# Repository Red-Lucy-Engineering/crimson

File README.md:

# "crimson" OSHW compact foldable mechanical keyboard

## Roadmap
- [x] Schematics mk1 finished
- [x] PCB design mk1 finished
- [ ] 3D printable Chassis designed in CAD
- [ ] Keycaps 3D printable in ABS
- [ ] firmware finished
- [ ] first version assembled irl
- [ ] first version thoroughly tested
- [ ] first version on sale

## Specs
- TKL -> 87 ULP Cherry Tactile Switches
- Foldable -> preferrably in thirds
- 3D printable chassis and caps
- ZMK firmware based on nice!nano V2 Microcontroller

## BOM

| Amount | Part                         |
|--------|------------------------------|
| 1      | crimson PCB                  |
| 86     | 1N4148W Diode                |
| 86     | Cherry ULP tactile switch    |
| 1      | 6mm tactile switch           |
| 1      | PCM12 SPDT switch            |
| 1      | nice!nano V2 microcontroller |
| 1      | 74HC595 TSSOP-16             |
| 1      | 0805 0,1uF capacitor         |
| 43     | Wires                        |

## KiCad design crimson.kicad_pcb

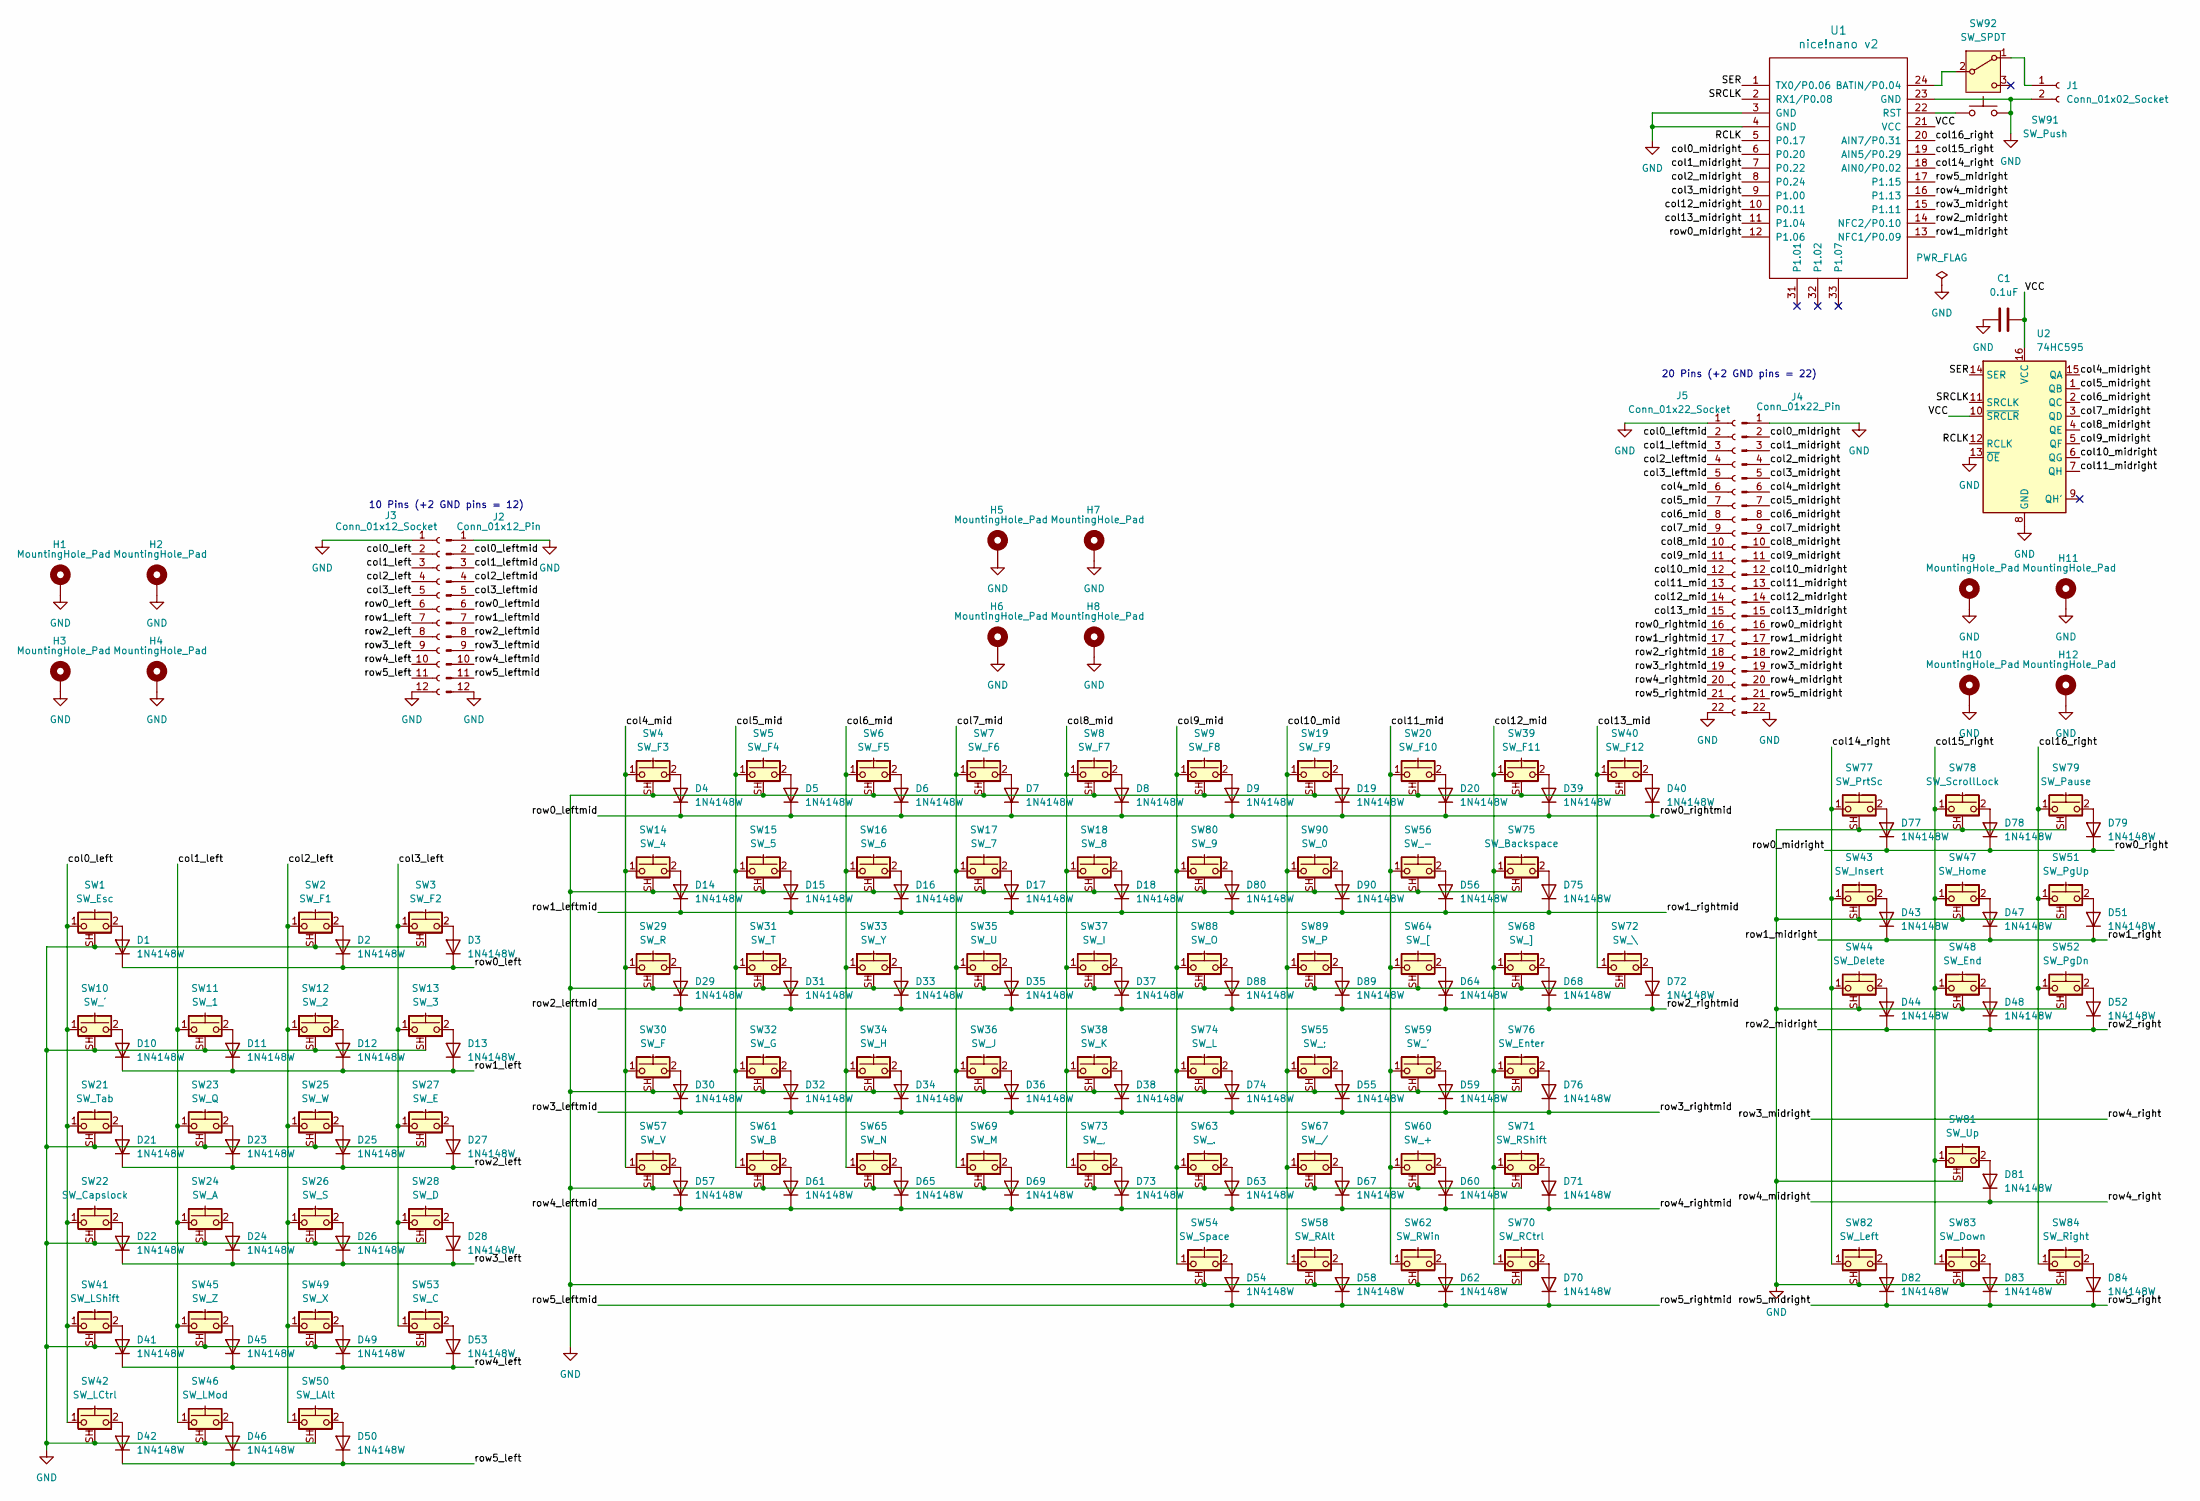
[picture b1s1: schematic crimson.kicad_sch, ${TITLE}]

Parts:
C1: 0.1uF; C_0805_2012Metric_Pad1.18x1.45mm_HandSolder
D1, D2, D3, D4, D5, D6, D7, D8, D9, D10, D11, D12, D13, D14, D15, D16, D17, D18, D19, D20, D21, D22, D23, D24, D25, D26, D27, D28, D29, D30, D31, D32, D33, D34, D35, D36, D37, D38, D39, D40, D41, D42, D43, D44, D45, D46, D47, D48, D49, D50, D51, D52, D53, D54, D55, D56, D57, D58, D59, D60, D61, D62, D63, D64, D65, D67, D68, D69, D70, D71, D72, D73, D74, D75, D76, D77, D78, D79, D80, D81, D82, D83, D84, D88, D89, D90: 1N4148W; D_SOD-123
H1, H2, H3, H4, H5, H6, H7, H8, H9, H10, H11, H12: MountingHole_Pad; MountingHole_2.2mm_M2_DIN965_Pad
J1: Conn_01x02_Socket; JST_PH_S2B-PH-K_1x02_P2.00mm_Horizontal
J2: Conn_01x12_Pin; PinHeader_1x12_P2.00mm_Vertical
J3: Conn_01x12_Socket; PinSocket_1x12_P2.00mm_Vertical
J4: Conn_01x22_Pin; PinSocket_1x22_P2.00mm_Vertical
J5: Conn_01x22_Socket; PinSocket_1x22_P2.00mm_Vertical
SW1: SW_Esc; Cherry_ULP_TH
SW2: SW_F1; Cherry_ULP_TH
SW3: SW_F2; Cherry_ULP_TH
SW4: SW_F3; Cherry_ULP_TH
SW5: SW_F4; Cherry_ULP_TH
SW6: SW_F5; Cherry_ULP_TH
SW7: SW_F6; Cherry_ULP_TH
SW8: SW_F7; Cherry_ULP_TH
SW9: SW_F8; Cherry_ULP_TH
SW10: SW_´; Cherry_ULP_TH
SW11: SW_1; Cherry_ULP_TH
SW12: SW_2; Cherry_ULP_TH
SW13: SW_3; Cherry_ULP_TH
SW14: SW_4; Cherry_ULP_TH
SW15: SW_5; Cherry_ULP_TH
SW16: SW_6; Cherry_ULP_TH
SW17: SW_7; Cherry_ULP_TH
SW18: SW_8; Cherry_ULP_TH
SW19: SW_F9; Cherry_ULP_TH
SW20: SW_F10; Cherry_ULP_TH
SW21: SW_Tab; Cherry_ULP_TH
SW22: SW_Capslock; Cherry_ULP_TH
SW23: SW_Q; Cherry_ULP_TH
SW24: SW_A; Cherry_ULP_TH
SW25: SW_W; Cherry_ULP_TH
SW26: SW_S; Cherry_ULP_TH
SW27: SW_E; Cherry_ULP_TH
SW28: SW_D; Cherry_ULP_TH
SW29: SW_R; Cherry_ULP_TH
SW30: SW_F; Cherry_ULP_TH
SW31: SW_T; Cherry_ULP_TH
SW32: SW_G; Cherry_ULP_TH
SW33: SW_Y; Cherry_ULP_TH
SW34: SW_H; Cherry_ULP_TH
SW35: SW_U; Cherry_ULP_TH
SW36: SW_J; Cherry_ULP_TH
SW37: SW_I; Cherry_ULP_TH
SW38: SW_K; Cherry_ULP_TH
SW39: SW_F11; Cherry_ULP_TH
SW40: SW_F12; Cherry_ULP_TH
SW41: SW_LShift; Cherry_ULP_TH
SW42: SW_LCtrl; Cherry_ULP_TH
SW43: SW_Insert; Cherry_ULP_TH
SW44: SW_Delete; Cherry_ULP_TH
SW45: SW_Z; Cherry_ULP_TH
SW46: SW_LMod; Cherry_ULP_TH
SW47: SW_Home; Cherry_ULP_TH
SW48: SW_End; Cherry_ULP_TH
SW49: SW_X; Cherry_ULP_TH
SW50: SW_LAlt; Cherry_ULP_TH
SW51: SW_PgUp; Cherry_ULP_TH
SW52: SW_PgDn; Cherry_ULP_TH
SW53: SW_C; Cherry_ULP_TH
SW54: SW_Space; Cherry_ULP_TH
SW55: SW_;; Cherry_ULP_TH
SW56: SW_-; Cherry_ULP_TH
SW57: SW_V; Cherry_ULP_TH
SW58: SW_RAlt; Cherry_ULP_TH
SW59: SW_'; Cherry_ULP_TH
SW60: SW_+; Cherry_ULP_TH
SW61: SW_B; Cherry_ULP_TH
SW62: SW_RWin; Cherry_ULP_TH
SW63: SW_.; Cherry_ULP_TH
SW64: SW_[; Cherry_ULP_TH
SW65: SW_N; Cherry_ULP_TH
SW67: SW_/; Cherry_ULP_TH
SW68: SW_]; Cherry_ULP_TH
SW69: SW_M; Cherry_ULP_TH
SW70: SW_RCtrl; Cherry_ULP_TH
SW71: SW_RShift; Cherry_ULP_TH
SW72: SW_\; Cherry_ULP_TH
SW73: SW_,; Cherry_ULP_TH
SW74: SW_L; Cherry_ULP_TH
SW75: SW_Backspace; Cherry_ULP_TH
SW76: SW_Enter; Cherry_ULP_TH
SW77: SW_PrtSc; Cherry_ULP_TH
SW78: SW_ScrollLock; Cherry_ULP_TH
SW79: SW_Pause; Cherry_ULP_TH
SW80: SW_9; Cherry_ULP_TH
SW81: SW_Up; Cherry_ULP_TH
SW82: SW_Left; Cherry_ULP_TH
SW83: SW_Down; Cherry_ULP_TH
SW84: SW_Right; Cherry_ULP_TH
SW88: SW_O; Cherry_ULP_TH
SW89: SW_P; Cherry_ULP_TH
SW90: SW_0; Cherry_ULP_TH
SW91: SW_Push; SW_PUSH_6mm
SW92: SW_SPDT; SW_SPDT_PCM12
U1: nice!nano v2; nice_nano
U2: 74HC595; TSSOP-16_4.4x5mm_P0.65mm

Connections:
/RCLK: U1.5 (P0.17), U2.12 (RCLK)
/SER: U1.1 (TX0/P0.06), U2.14 (SER)
/SRCLK: U1.2 (RX1/P0.08), U2.11 (SRCLK)
/VCC: C1.2, U1.21 (VCC), U2.10 (~SRCLR), U2.16 (VCC)
/col0_left: J3.2, SW1.1, SW10.1, SW21.1, SW22.1, SW41.1, SW42.1
/col0_leftmid: J2.2, J5.2
/col0_midright: J4.2, U1.6 (P0.20)
/col1_left: J3.3, SW11.1, SW23.1, SW24.1, SW45.1, SW46.1
/col1_leftmid: J2.3, J5.3
/col1_midright: J4.3, U1.7 (P0.22)
/col2_left: J3.4, SW2.1, SW12.1, SW25.1, SW26.1, SW49.1, SW50.1
/col2_leftmid: J2.4, J5.4
/col2_midright: J4.4, U1.8 (P0.24)
/col3_left: J3.5, SW3.1, SW13.1, SW27.1, SW28.1, SW53.1
/col3_leftmid: J2.5, J5.5
/col3_midright: J4.5, U1.9 (P1.00)
/col4_mid: J5.6, SW4.1, SW14.1, SW29.1, SW30.1, SW57.1
/col4_midright: J4.6, U2.15 (QA)
/col5_mid: J5.7, SW5.1, SW15.1, SW31.1, SW32.1, SW61.1
/col5_midright: J4.7, U2.1 (QB)
/col6_mid: J5.8, SW6.1, SW16.1, SW33.1, SW34.1, SW65.1
/col6_midright: J4.8, U2.2 (QC)
/col7_mid: J5.9, SW7.1, SW17.1, SW35.1, SW36.1, SW69.1
/col7_midright: J4.9, U2.3 (QD)
/col8_mid: J5.10, SW8.1, SW18.1, SW37.1, SW38.1, SW73.1
/col8_midright: J4.10, U2.4 (QE)
/col9_mid: J5.11, SW9.1, SW54.1, SW63.1, SW74.1, SW80.1, SW88.1
/col9_midright: J4.11, U2.5 (QF)
/col10_mid: J5.12, SW19.1, SW55.1, SW58.1, SW67.1, SW89.1, SW90.1
/col10_midright: J4.12, U2.6 (QG)
/col11_mid: J5.13, SW20.1, SW56.1, SW59.1, SW60.1, SW62.1, SW64.1
/col11_midright: J4.13, U2.7 (QH)
/col12_mid: J5.14, SW39.1, SW68.1, SW70.1, SW71.1, SW75.1, SW76.1
/col12_midright: J4.14, U1.10 (P0.11)
/col13_mid: J5.15, SW40.1, SW72.1
/col13_midright: J4.15, U1.11 (P1.04)
/col14_right: SW43.1, SW44.1, SW77.1, SW82.1, U1.18 (AIN0/P0.02)
/col15_right: SW47.1, SW48.1, SW78.1, SW81.1, SW83.1, U1.19 (AIN5/P0.29)
/col16_right: SW51.1, SW52.1, SW79.1, SW84.1, U1.20 (AIN7/P0.31)
/row0_left: D1.1 (K), D2.1 (K), D3.1 (K), J3.6
/row0_leftmid: D4.1 (K), D5.1 (K), D6.1 (K), D7.1 (K), D8.1 (K), D9.1 (K), D19.1 (K), D20.1 (K), D39.1 (K), D40.1 (K), J2.6, J5.16
/row0_midright: D77.1 (K), D78.1 (K), D79.1 (K), J4.16, U1.12 (P1.06)
/row1_left: D10.1 (K), D11.1 (K), D12.1 (K), D13.1 (K), J3.7
/row1_leftmid: D14.1 (K), D15.1 (K), D16.1 (K), D17.1 (K), D18.1 (K), D56.1 (K), D75.1 (K), D80.1 (K), D90.1 (K), J2.7, J5.17
/row1_midright: D43.1 (K), D47.1 (K), D51.1 (K), J4.17, U1.13 (NFC1/P0.09)
/row2_left: D21.1 (K), D23.1 (K), D25.1 (K), D27.1 (K), J3.8
/row2_leftmid: D29.1 (K), D31.1 (K), D33.1 (K), D35.1 (K), D37.1 (K), D64.1 (K), D68.1 (K), D72.1 (K), D88.1 (K), D89.1 (K), J2.8, J5.18
/row2_midright: D44.1 (K), D48.1 (K), D52.1 (K), J4.18, U1.14 (NFC2/P0.10)
/row3_left: D22.1 (K), D24.1 (K), D26.1 (K), D28.1 (K), J3.9
/row3_leftmid: D30.1 (K), D32.1 (K), D34.1 (K), D36.1 (K), D38.1 (K), D55.1 (K), D59.1 (K), D74.1 (K), D76.1 (K), J2.9, J5.19
/row3_midright: D81.1 (K), J4.19, J4.20, U1.15 (P1.11), U1.16 (P1.13)
/row4_left: D41.1 (K), D45.1 (K), D49.1 (K), D53.1 (K), J3.10
/row4_leftmid: D57.1 (K), D60.1 (K), D61.1 (K), D63.1 (K), D65.1 (K), D67.1 (K), D69.1 (K), D71.1 (K), D73.1 (K), J2.10, J5.20
/row5_left: D42.1 (K), D46.1 (K), D50.1 (K), J3.11
/row5_leftmid: D54.1 (K), D58.1 (K), D62.1 (K), D70.1 (K), J2.11, J5.21
/row5_midright: D82.1 (K), D83.1 (K), D84.1 (K), J4.21, U1.17 (P1.15)
GND: C1.1, H1.1 (1_1), H2.1 (1_1), H3.1 (1_1), H4.1 (1_1), H5.1 (1_1), H6.1 (1_1), H7.1 (1_1), H8.1 (1_1), H9.1 (1_1), H10.1 (1_1), H11.1 (1_1), H12.1 (1_1), J1.2, J2.1, J2.12, J3.1, J3.12, J4.1, J4.22, J5.1, J5.22, SW1.SH (B), SW2.SH (B), SW3.SH (B), SW4.SH (B), SW5.SH (B), SW6.SH (B), SW7.SH (B), SW8.SH (B), SW9.SH (B), SW10.SH (B), SW11.SH (B), SW12.SH (B), SW13.SH (B), SW14.SH (B), SW15.SH (B), SW16.SH (B), SW17.SH (B), SW18.SH (B), SW19.SH (B), SW20.SH (B), SW21.SH (B), SW22.SH (B), SW23.SH (B), SW24.SH (B), SW25.SH (B), SW26.SH (B), SW27.SH (B), SW28.SH (B), SW29.SH (B), SW30.SH (B), SW31.SH (B), SW32.SH (B), SW33.SH (B), SW34.SH (B), SW35.SH (B), SW36.SH (B), SW37.SH (B), SW38.SH (B), SW39.SH (B), SW40.SH (B), SW41.SH (B), SW42.SH (B), SW43.SH (B), SW44.SH (B), SW45.SH (B), SW46.SH (B), SW47.SH (B), SW48.SH (B), SW49.SH (B), SW50.SH (B), SW51.SH (B), SW52.SH (B), SW53.SH (B), SW54.SH (B), SW55.SH (B), SW56.SH (B), SW57.SH (B), SW58.SH (B), SW59.SH (B), SW60.SH (B), SW61.SH (B), SW62.SH (B), SW63.SH (B), SW64.SH (B), SW65.SH (B), SW67.SH (B), SW68.SH (B), SW69.SH (B), SW70.SH (B), SW71.SH (B), SW72.SH (B), SW73.SH (B), SW74.SH (B), SW75.SH (B), SW76.SH (B), SW77.SH (B), SW78.SH (B), SW79.SH (B), SW80.SH (B), SW81.SH (B), SW82.SH (B), SW83.SH (B), SW84.SH (B), SW88.SH (B), SW89.SH (B), SW90.SH (B), SW91.2, U1.3 (GND), U1.4 (GND), U1.23 (GND), U2.8 (GND), U2.13 (~OE)
unnamed: D1.2 (A), SW1.2
unnamed: D2.2 (A), SW2.2
unnamed: D3.2 (A), SW3.2
unnamed: D4.2 (A), SW4.2
unnamed: D5.2 (A), SW5.2
unnamed: D6.2 (A), SW6.2
unnamed: D7.2 (A), SW7.2
unnamed: D8.2 (A), SW8.2
unnamed: D9.2 (A), SW9.2
unnamed: D10.2 (A), SW10.2
unnamed: D11.2 (A), SW11.2
unnamed: D12.2 (A), SW12.2
unnamed: D13.2 (A), SW13.2
unnamed: D14.2 (A), SW14.2
unnamed: D15.2 (A), SW15.2
unnamed: D16.2 (A), SW16.2
unnamed: D17.2 (A), SW17.2
unnamed: D18.2 (A), SW18.2
unnamed: D19.2 (A), SW19.2
unnamed: D20.2 (A), SW20.2
unnamed: D21.2 (A), SW21.2
unnamed: D22.2 (A), SW22.2
unnamed: D23.2 (A), SW23.2
unnamed: D24.2 (A), SW24.2
unnamed: D25.2 (A), SW25.2
unnamed: D26.2 (A), SW26.2
unnamed: D27.2 (A), SW27.2
unnamed: D28.2 (A), SW28.2
unnamed: D29.2 (A), SW29.2
unnamed: D30.2 (A), SW30.2
unnamed: D31.2 (A), SW31.2
unnamed: D32.2 (A), SW32.2
unnamed: D33.2 (A), SW33.2
unnamed: D34.2 (A), SW34.2
unnamed: D35.2 (A), SW35.2
unnamed: D36.2 (A), SW36.2
unnamed: D37.2 (A), SW37.2
unnamed: D38.2 (A), SW38.2
unnamed: D39.2 (A), SW39.2
unnamed: D40.2 (A), SW40.2
unnamed: D41.2 (A), SW41.2
unnamed: D42.2 (A), SW42.2
unnamed: D43.2 (A), SW43.2
unnamed: D44.2 (A), SW44.2
unnamed: D45.2 (A), SW45.2
unnamed: D46.2 (A), SW46.2
unnamed: D47.2 (A), SW47.2
unnamed: D48.2 (A), SW48.2
unnamed: D49.2 (A), SW49.2
unnamed: D50.2 (A), SW50.2
unnamed: D51.2 (A), SW51.2
unnamed: D52.2 (A), SW52.2
unnamed: D53.2 (A), SW53.2
unnamed: D54.2 (A), SW54.2
unnamed: D55.2 (A), SW55.2
unnamed: D56.2 (A), SW56.2
unnamed: D57.2 (A), SW57.2
unnamed: D58.2 (A), SW58.2
unnamed: D59.2 (A), SW59.2
unnamed: D60.2 (A), SW60.2
unnamed: D61.2 (A), SW61.2
unnamed: D62.2 (A), SW62.2
unnamed: D63.2 (A), SW63.2
unnamed: D64.2 (A), SW64.2
unnamed: D65.2 (A), SW65.2
unnamed: D67.2 (A), SW67.2
unnamed: D68.2 (A), SW68.2
unnamed: D69.2 (A), SW69.2
unnamed: D70.2 (A), SW70.2
unnamed: D71.2 (A), SW71.2
unnamed: D72.2 (A), SW72.2
unnamed: D73.2 (A), SW73.2
unnamed: D74.2 (A), SW74.2
unnamed: D75.2 (A), SW75.2
unnamed: D76.2 (A), SW76.2
unnamed: D77.2 (A), SW77.2
unnamed: D78.2 (A), SW78.2
unnamed: D79.2 (A), SW79.2
unnamed: D80.2 (A), SW80.2
unnamed: D81.2 (A), SW81.2
unnamed: D82.2 (A), SW82.2
unnamed: D83.2 (A), SW83.2
unnamed: D84.2 (A), SW84.2
unnamed: D88.2 (A), SW88.2
unnamed: D89.2 (A), SW89.2
unnamed: D90.2 (A), SW90.2
unnamed: J1.1, SW92.1 (A)
unnamed: SW92.2 (B), U1.24 (BATIN/P0.04)
unnamed: SW91.1, U1.22 (RST)

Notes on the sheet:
10 Pins (+2 GND pins = 12)
20 Pins (+2 GND pins = 22)

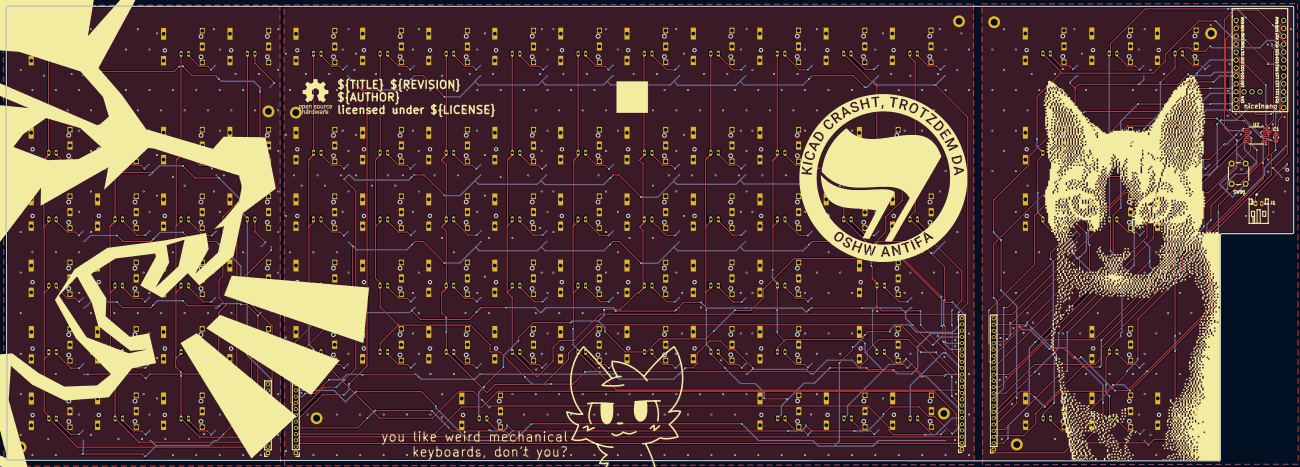
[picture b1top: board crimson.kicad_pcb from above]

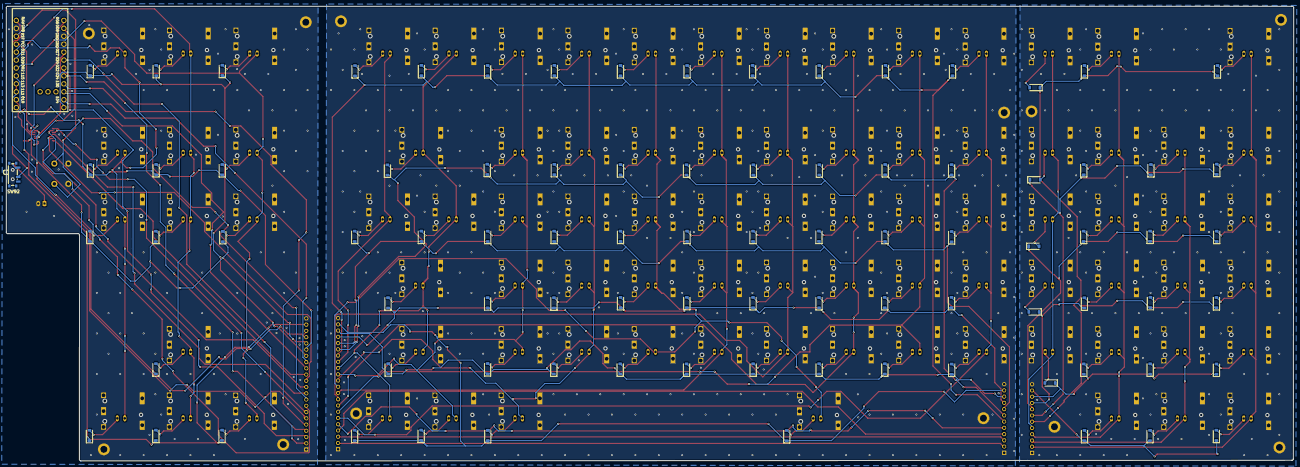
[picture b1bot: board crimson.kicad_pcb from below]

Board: 4 copper layers, 412.3 x 145.6 mm, 194 parts (87 on the bottom side), 146 nets.

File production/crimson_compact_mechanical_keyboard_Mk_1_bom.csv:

Designator,Footprint,Quantity,Value,LCSC Part #
C1,0805,1,0.1uF,
"D1, D10, D11, D12, D13, D14, D15, D16, D17, D18, D19, D2, D20, D21, D22, D23, D24, D25, D26, D27, D28, D29, D3, D30, D31, D32, D33, D34, D35, D36, D37, D38, D39, D4, D40, D41, D42, D43, D44, D45, D46, D47, D48, D49, D5, D50, D51, D52, D53, D54, D55, D56, D57, D58, D59, D6, D60, D61, D62, D63, D64, D65, D67, D68, D69, D7, D70, D71, D72, D73, D74, D75, D76, D77, D78, D79, D8, D80, D81, D82, D83, D84, D88, D89, D9, D90",D_SOD-123,86,1N4148W,
J1,JST_PH_S2B-PH-K_1x02_P2.00mm_Horizontal,1,Conn_01x02_Socket,
J2,PinHeader_1x12_P2.00mm_Vertical,1,Conn_01x12_Pin,
J3,PinSocket_1x12_P2.00mm_Vertical,1,Conn_01x12_Socket,
J4,PinSocket_1x22_P2.00mm_Vertical,1,Conn_01x22_Pin,
J5,PinSocket_1x22_P2.00mm_Vertical,1,Conn_01x22_Socket,
SW1,Cherry_ULP_TH,1,SW_Esc,
SW10,Cherry_ULP_TH,1,SW_´,
SW11,Cherry_ULP_TH,1,SW_1,
SW12,Cherry_ULP_TH,1,SW_2,
SW13,Cherry_ULP_TH,1,SW_3,
SW14,Cherry_ULP_TH,1,SW_4,
SW15,Cherry_ULP_TH,1,SW_5,
SW16,Cherry_ULP_TH,1,SW_6,
SW17,Cherry_ULP_TH,1,SW_7,
SW18,Cherry_ULP_TH,1,SW_8,
SW19,Cherry_ULP_TH,1,SW_F9,
SW2,Cherry_ULP_TH,1,SW_F1,
SW20,Cherry_ULP_TH,1,SW_F10,
SW21,Cherry_ULP_TH,1,SW_Tab,
SW22,Cherry_ULP_TH,1,SW_Capslock,
SW23,Cherry_ULP_TH,1,SW_Q,
SW24,Cherry_ULP_TH,1,SW_A,
SW25,Cherry_ULP_TH,1,SW_W,
SW26,Cherry_ULP_TH,1,SW_S,
SW27,Cherry_ULP_TH,1,SW_E,
SW28,Cherry_ULP_TH,1,SW_D,
SW29,Cherry_ULP_TH,1,SW_R,
SW3,Cherry_ULP_TH,1,SW_F2,
SW30,Cherry_ULP_TH,1,SW_F,
SW31,Cherry_ULP_TH,1,SW_T,
SW32,Cherry_ULP_TH,1,SW_G,
SW33,Cherry_ULP_TH,1,SW_Y,
SW34,Cherry_ULP_TH,1,SW_H,
SW35,Cherry_ULP_TH,1,SW_U,
SW36,Cherry_ULP_TH,1,SW_J,
SW37,Cherry_ULP_TH,1,SW_I,
SW38,Cherry_ULP_TH,1,SW_K,
SW39,Cherry_ULP_TH,1,SW_F11,
SW4,Cherry_ULP_TH,1,SW_F3,
SW40,Cherry_ULP_TH,1,SW_F12,
SW41,Cherry_ULP_TH,1,SW_LShift,
SW42,Cherry_ULP_TH,1,SW_LCtrl,
SW43,Cherry_ULP_TH,1,SW_Insert,
SW44,Cherry_ULP_TH,1,SW_Delete,
SW45,Cherry_ULP_TH,1,SW_Z,
SW46,Cherry_ULP_TH,1,SW_LMod,
SW47,Cherry_ULP_TH,1,SW_Home,
SW48,Cherry_ULP_TH,1,SW_End,
SW49,Cherry_ULP_TH,1,SW_X,
SW5,Cherry_ULP_TH,1,SW_F4,
SW50,Cherry_ULP_TH,1,SW_LAlt,
SW51,Cherry_ULP_TH,1,SW_PgUp,
SW52,Cherry_ULP_TH,1,SW_PgDn,
SW53,Cherry_ULP_TH,1,SW_C,
SW54,Cherry_ULP_TH,1,SW_Space,
SW55,Cherry_ULP_TH,1,SW_;,
SW56,Cherry_ULP_TH,1,SW_-,
SW57,Cherry_ULP_TH,1,SW_V,
SW58,Cherry_ULP_TH,1,SW_RAlt,
SW59,Cherry_ULP_TH,1,SW_',
SW6,Cherry_ULP_TH,1,SW_F5,
SW60,Cherry_ULP_TH,1,SW_+,
SW61,Cherry_ULP_TH,1,SW_B,
SW62,Cherry_ULP_TH,1,SW_RWin,
SW63,Cherry_ULP_TH,1,SW_.,
SW64,Cherry_ULP_TH,1,SW_[,
SW65,Cherry_ULP_TH,1,SW_N,
SW67,Cherry_ULP_TH,1,SW_/,
SW68,Cherry_ULP_TH,1,SW_],
SW69,Cherry_ULP_TH,1,SW_M,
SW7,Cherry_ULP_TH,1,SW_F6,
SW70,Cherry_ULP_TH,1,SW_RCtrl,
SW71,Cherry_ULP_TH,1,SW_RShift,
SW72,Cherry_ULP_TH,1,SW_\,
SW73,Cherry_ULP_TH,1,"SW_,",
SW74,Cherry_ULP_TH,1,SW_L,
SW75,Cherry_ULP_TH,1,SW_Backspace,
SW76,Cherry_ULP_TH,1,SW_Enter,
SW77,Cherry_ULP_TH,1,SW_PrtSc,
SW78,Cherry_ULP_TH,1,SW_ScrollLock,
SW79,Cherry_ULP_TH,1,SW_Pause,
SW8,Cherry_ULP_TH,1,SW_F7,
SW80,Cherry_ULP_TH,1,SW_9,
SW81,Cherry_ULP_TH,1,SW_Up,
SW82,Cherry_ULP_TH,1,SW_Left,
SW83,Cherry_ULP_TH,1,SW_Down,
SW84,Cherry_ULP_TH,1,SW_Right,
SW88,Cherry_ULP_TH,1,SW_O,
SW89,Cherry_ULP_TH,1,SW_P,
SW9,Cherry_ULP_TH,1,SW_F8,
SW90,Cherry_ULP_TH,1,SW_0,
SW91,SW_PUSH_6mm,1,SW_Push,
SW92,SW_SPDT_PCM12,1,SW_SPDT,
U1,nice_nano,1,nice!nano v2,
U2,TSSOP-16_4.4x5mm_P0.65mm,1,74HC595,

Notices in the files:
crimson.kicad_pcb:
licensed under ${LICENSE}
parts and their libraries:
LICENSE: CC-BY
